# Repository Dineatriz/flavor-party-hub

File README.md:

🎮 Flavor Party Hub

Flavor Party Hub is a DIY party game console where the TV is the screen and players' phones are the controllers, no app install needed, everything runs in the browser.

🕹️ How It Works

When the TV opens the app, the server automatically creates a room with a unique code and QR Code. Players scan the QR Code or type the code in their phone's browser to join. The first player to join becomes the Host and controls the game from the TV.

All communication between the TV and phones happens through a Node.js + Socket.io server using WebSockets — this is what makes everything update in real time.

🎯 Mini-Games

🧠 The Brainiac (Quiz)
The Brainiac is a speed quiz where the question appears on the TV with 4 colored options. Players answer using symbol buttons on their phones without seeing the text forcing them to look at the TV. Points are calculated based on speed and correctness.

⚡ Nitro Click (Reaction Test)
The screen turns red u need to wait for green, then click as fast as possible. Click before the green appears and you're eliminated for that round.

🎨 Doodle Dash (Drawing)
One player gets a secret word and draws it on their phone. The drawing appears in real time on the TV while other players type their guesses.(similar to gartic)

🏗️ Architecture
```
flavor-party-hub/
├── server/
│   ├── index.js          ← Express + Socket.io server
│   ├── roomManager.js    ← Room and player management
│   └── gameLogic.js      ← Game rules for all 3 mini-games
├── tv-client/
│   └── index.html        ← TV interface
└── mobile-client/
    └── index.html        ← Phone controller interface
```

🔧 Hardware

This software is designed to run on a **Raspberry Pi 5** connected to a TV via HDMI. The Raspberry Pi sits inside a custom 3D printed case and connects to a custom PCB featuring:

- 8 LEDs for visual effects
- 1 buzzer for sound feedback  
- 2 push buttons
- Custom JST connectors

The PCB was designed in KiCad and connects directly to the Raspberry Pi via the 40-pin GPIO header.

🚀 Setup
```bash
cd server
npm install
npm start
```

Then open `http://localhost:3000/tv` on the TV and `http://[LOCAL_IP]:3000/mobile` on phones.

📦 Dependencies

- Node.js
- Express
- Socket.io
- QRCode

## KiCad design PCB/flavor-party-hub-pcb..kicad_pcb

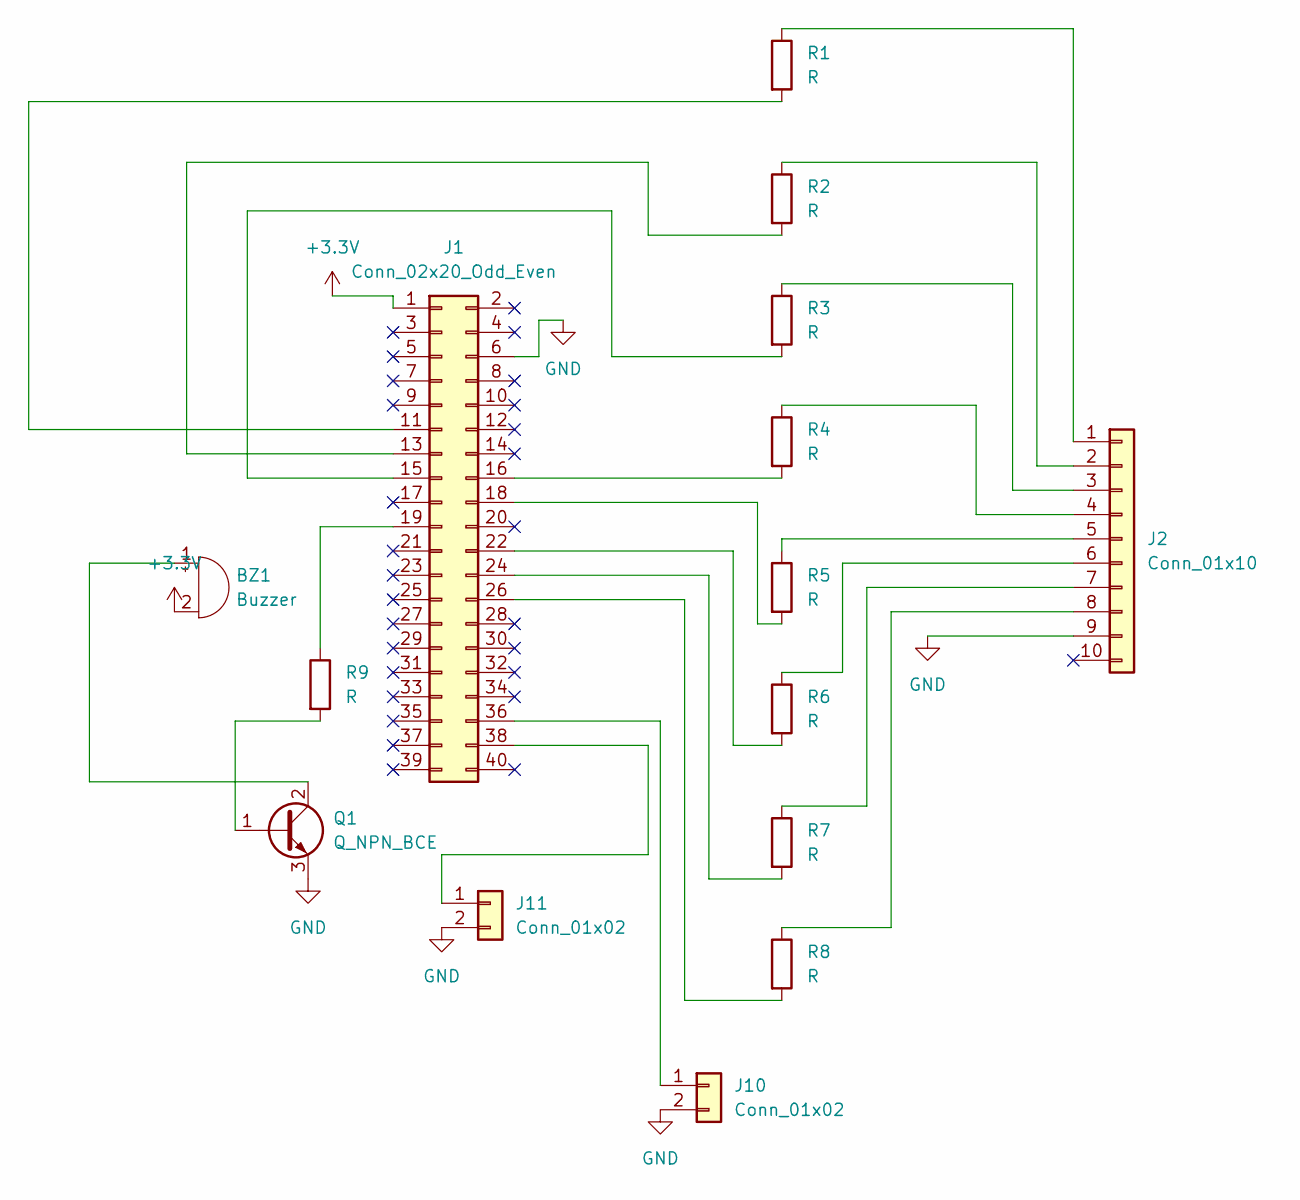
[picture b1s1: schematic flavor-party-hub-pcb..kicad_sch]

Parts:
BZ1: Buzzer; Buzzer_TDK_PS1240P02BT_D12.2mm_H6.5mm
J1: Conn_02x20_Odd_Even; PinHeader_2x20_P2.54mm_Vertical
J2: Conn_01x10; PinHeader_1x10_P2.54mm_Vertical
J10, J11: Conn_01x02; JST_PH_B2B-PH-K_1x02_P2.00mm_Vertical
Q1: Q_NPN_BCE; TO-92_Inline
R1, R2, R3, R4, R5, R6, R7, R8: R; R_Axial_DIN0207_L6.3mm_D2.5mm_P10.16mm_Horizontal
R9: R; R_Axial_DIN0207_L6.3mm_D2.5mm_P7.62mm_Horizontal

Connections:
+3.3V: BZ1.2 (-), J1.1
GND: J1.6, J2.9, J10.2, J11.2, Q1.3 (E)
unnamed: BZ1.1 (+), Q1.2 (C)
unnamed: J1.11, R1.2
unnamed: J1.13, R2.2
unnamed: J1.15, R3.2
unnamed: J1.16, R4.2
unnamed: J1.18, R5.2
unnamed: J1.19, R9.1
unnamed: J1.22, R6.2
unnamed: J1.24, R7.2
unnamed: J1.26, R8.2
unnamed: J1.36, J10.1
unnamed: J1.38, J11.1
unnamed: J2.1, R1.1
unnamed: J2.2, R2.1
unnamed: J2.3, R3.1
unnamed: J2.4, R4.1
unnamed: J2.5, R5.1
unnamed: J2.6, R6.1
unnamed: J2.7, R7.1
unnamed: J2.8, R8.1
unnamed: Q1.1 (B), R9.2

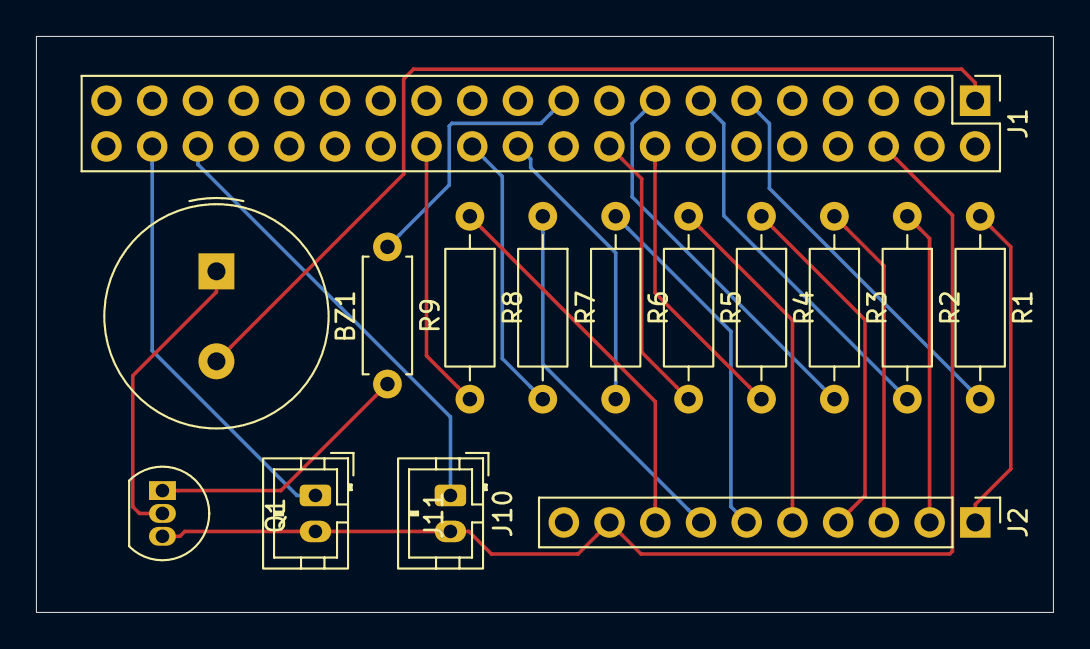
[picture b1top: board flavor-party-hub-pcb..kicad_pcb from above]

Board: 2 copper layers, 56.5 x 32.0 mm, 15 parts (0 on the bottom side), 23 nets.

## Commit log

2026-03-15 Initial commit - FlavorTown Party Hub with 3 mini-games
2026-03-15 Update README with project details and setup instructions
    Added detailed project description, mini-games, architecture, hardware requirements, setup instructions, and dependencies.
2026-03-15 Add README and screenshots
2026-03-15 Rename Captura de ecrã 2026-03-13 194143.png to pcb
2026-03-15 Rename Captura de ecrã 2026-03-14 160233.png to pcb 3d
2026-03-15 Rename Captura de ecrã 2026-03-14 161959.png to CAD_2
2026-03-15 Rename Captura de ecrã 2026-03-14 162008.png to CAD_1
2026-03-15 Rename Captura de ecrã 2026-03-15 222750.png to lobby
2026-03-15 Rename Captura de ecrã 2026-03-15 222903.png to doodle dash
2026-03-15 Rename Captura de ecrã 2026-03-15 222924.png to scoreboard
2026-03-15 Rename Captura de ecrã 2026-03-15 225649.png to quiz
2026-03-15 Rename Captura de ecrã 2026-03-15 225709.png to nitro click
2026-03-15 Rename CAD_1 to CAD_1.png
2026-03-15 Rename CAD_2 to CAD_2.png
2026-03-15 Rename doodle dash to doodle dash.png
2026-03-15 Rename lobby to lobby.png
2026-03-15 Rename nitro click to nitro click.png
2026-03-15 Rename pcb to pcb.png
2026-03-15 Rename pcb 3d to pcb 3d.png
2026-03-15 Rename quiz to quiz.png
2026-03-15 Rename scoreboard to scoreboard.png
2026-03-15 Add lobby screenshot to README
    Added a screenshot of the lobby to the README.
2026-03-15 Update README with game descriptions and screenshots
    Added screenshots for quiz, reaction test, and drawing sections.
2026-03-16 Rename doodle dash.png to doodle-dash.png
2026-03-16 Rename nitro click.png to nitro-click.png
2026-03-16 Rename pcb 3d.png to pcb-3d.png
2026-03-16 Fix screenshot filenames in README.md
    Corrected screenshot file names for Nitro Click and Doodle Dash.
2026-03-16 Fix screenshot filename in README.md
    Corrected the screenshot filename to match the actual file.
2026-03-16 Add CAD images to hardware section of README
    Added images of the CAD design to the README.
2026-03-16 Add PCB images and update setup section
    Add images of the PCB to the README and update setup instructions.
2026-03-16 Fix image display in README.md
2026-03-16 Add scoreboard image to README
2026-03-16 Adiciona pastas de CAD, PCB e ficheiros Gerber
